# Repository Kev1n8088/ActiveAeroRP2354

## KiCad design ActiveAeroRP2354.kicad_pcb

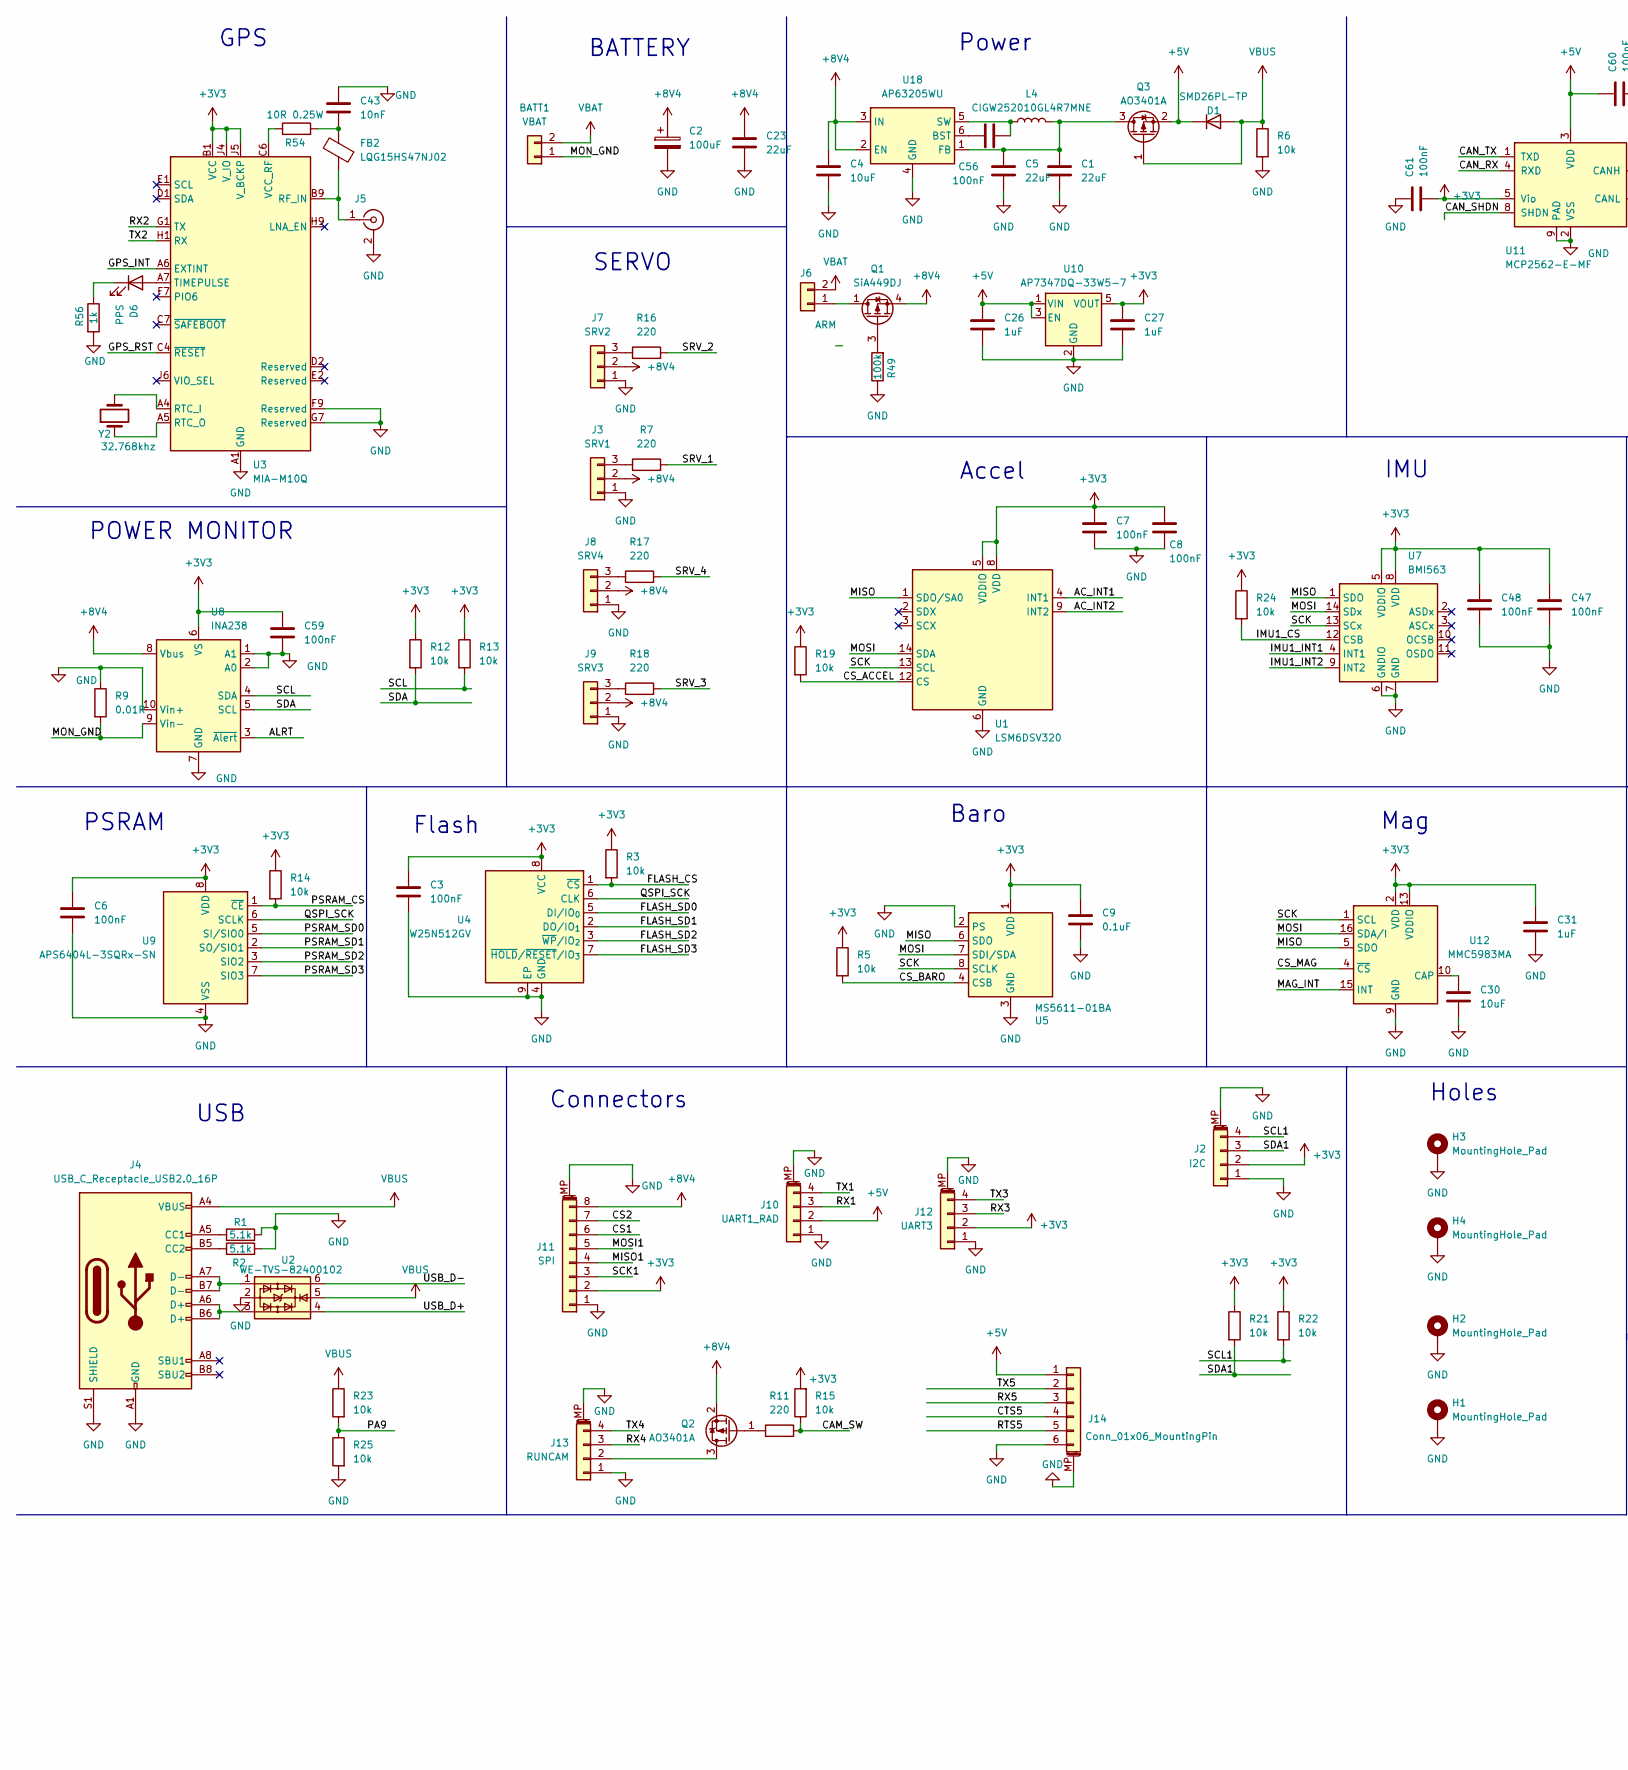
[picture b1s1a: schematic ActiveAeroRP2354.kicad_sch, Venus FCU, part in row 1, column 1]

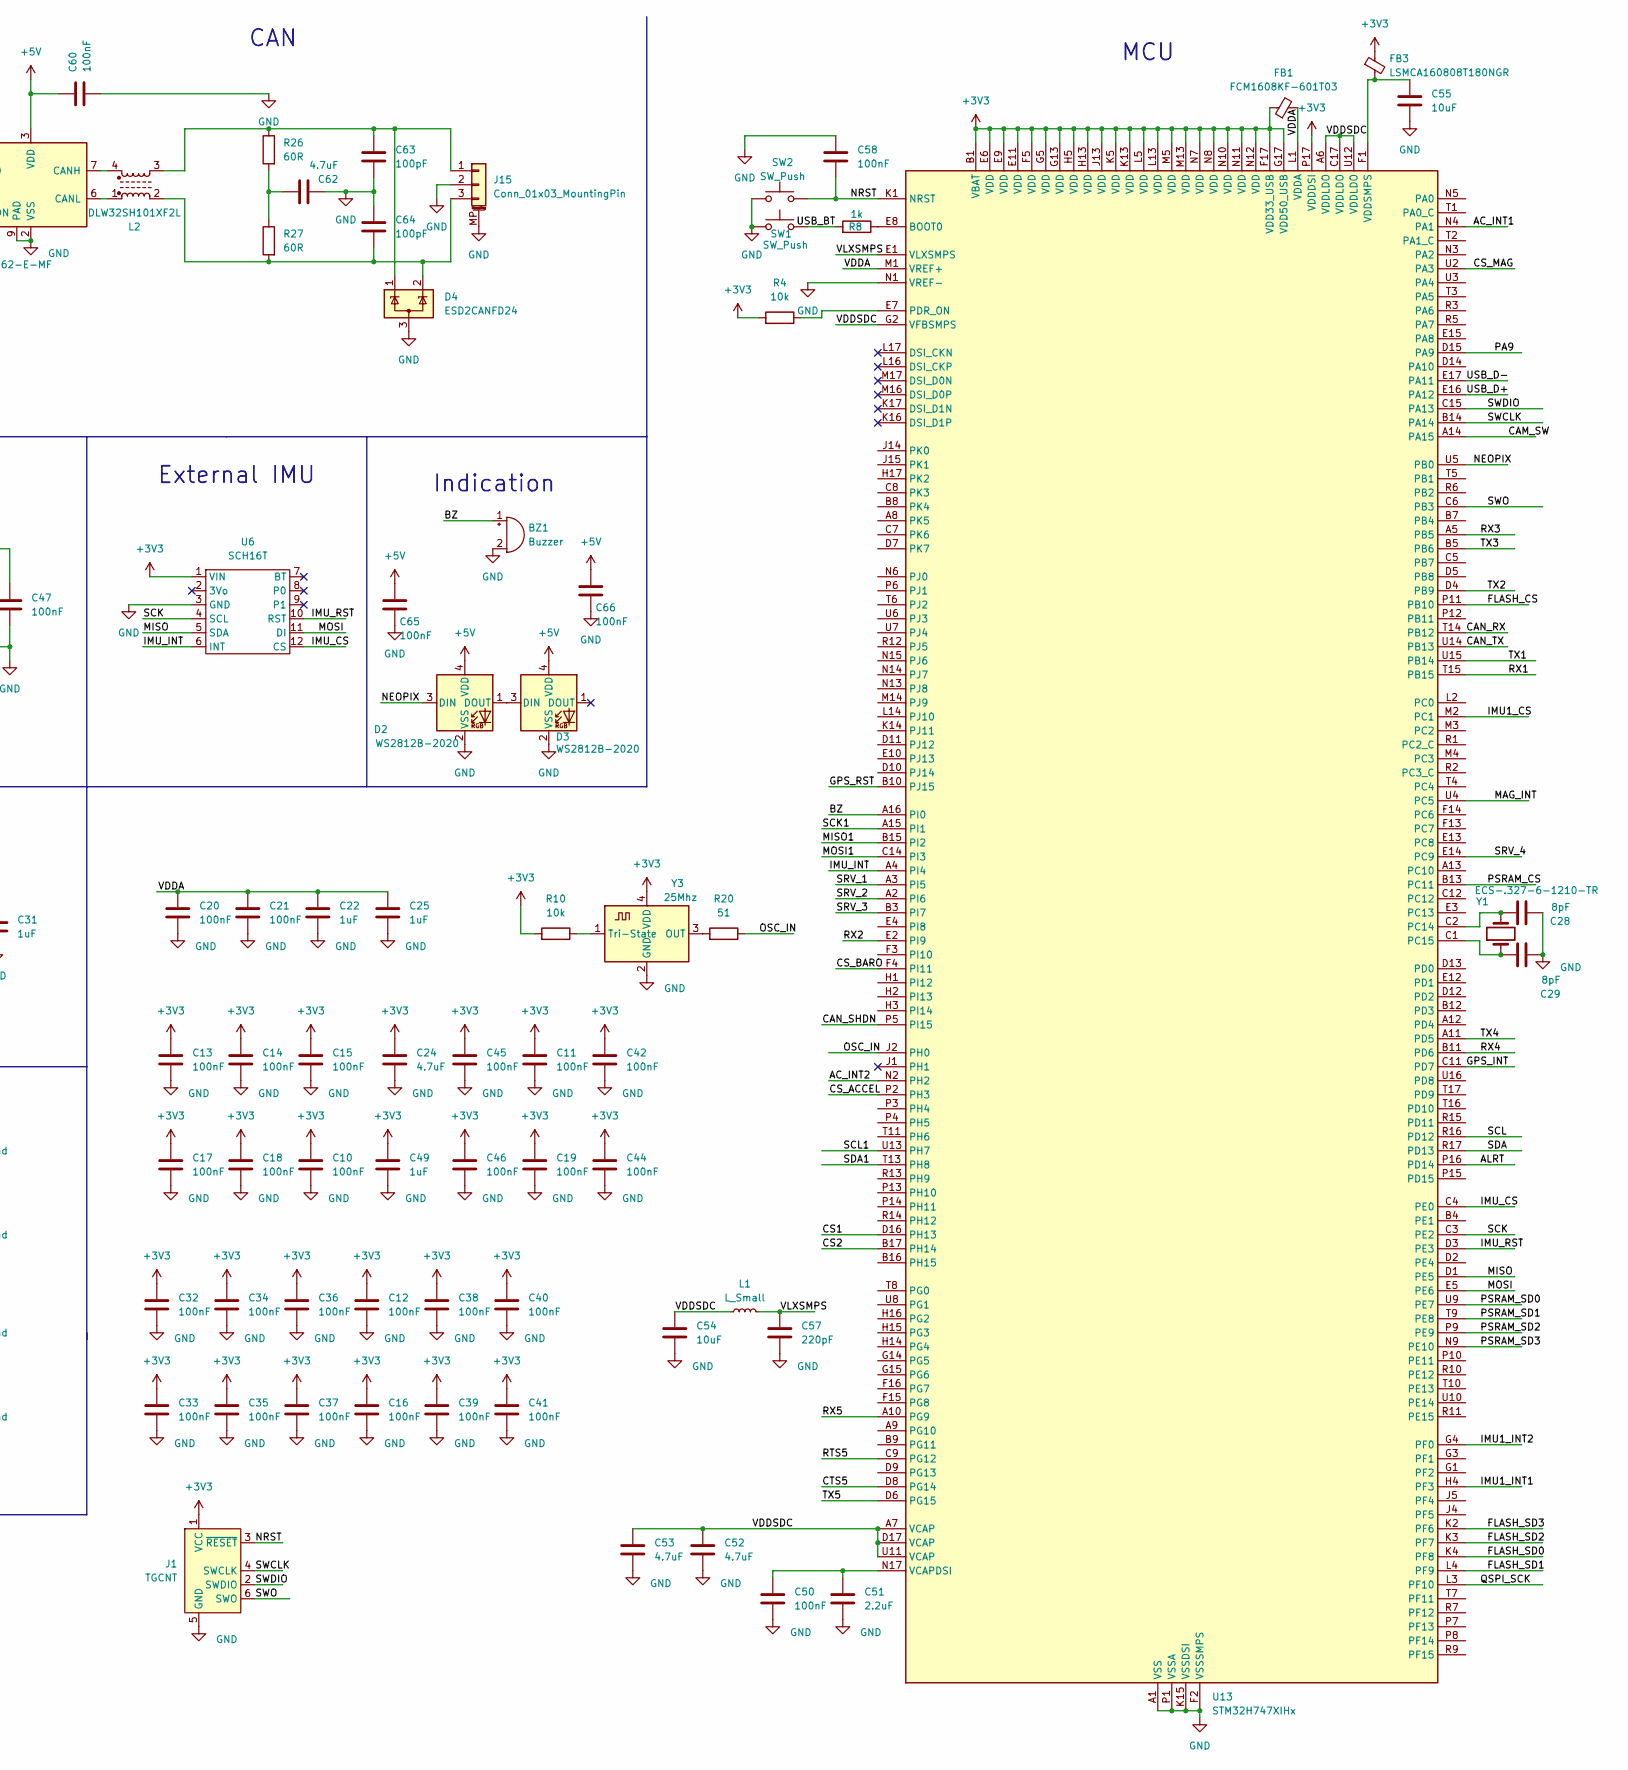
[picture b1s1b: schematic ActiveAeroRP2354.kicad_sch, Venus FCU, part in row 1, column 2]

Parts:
BATT1: VBAT; AMASS_XT30U-F_1x02_P5.0mm_Vertical
BZ1: Buzzer; Buzzer_CUI_CPT-9019S-SMT
C1, C5, C23: 22uF; C_0603_1608Metric
C2: 100uF; CP_Radial_D8.0mm_P5.00mm
C3, C6, C7, C8, C10, C11, C12, C13, C14, C15, C16, C17, C18, C19, C20, C21, C32, C33, C34, C35, C36, C37, C38, C39, C40, C41, C42, C44, C45, C46, C47, C48, C50, C56, C58, C59, C60, C61, C65, C66: 100nF; C_0402_1005Metric
C4, C30, C54, C55: 10uF; C_0402_1005Metric
C9: 0.1uF; C_0402_1005Metric
C22, C25, C26, C27, C31, C49: 1uF; C_0402_1005Metric
C24, C52, C53, C62: 4.7uF; C_0402_1005Metric
C28, C29: 8pF; C_0402_1005Metric
C43: 10nF; C_0402_1005Metric
C51: 2.2uF; C_0402_1005Metric
C57: 220pF; C_0402_1005Metric
C63, C64: 100pF; C_0402_1005Metric
D1: SMD26PL-TP; D_SOD-123F
D2, D3: WS2812B-2020; LED_WS2812B-2020_PLCC4_2.0x2.0mm
D4: ESD2CANFD24; SOT-23-3
D6: PPS; LED_0402_1005Metric
FB1: FCM1608KF-601T03; L_0402_1005Metric
FB2: LQG15HS47NJ02; L_0402_1005Metric
FB3: LSMCA160808T180NGR; L_0603_1608Metric
H1, H2, H3, H4: MountingHole_Pad; MountingHole_3.2mm_M3_DIN965_Pad
J1: TGCNT; Tag-Connect_TC2030-IDC-NL_2x03_P1.27mm_Vertical
J2: I2C; JST_SH_SM04B-SRSS-TB_1x04-1MP_P1.00mm_Horizontal
J3: SRV1; PinSocket_1x03_P2.54mm_Vertical
J4: USB_C_Receptacle_USB2.0_16P; USB_C_Receptacle_GCT_USB4110
J5: UFL; U.FL_Molex_MCRF_73412-0110_Vertical
J6: ARM; JST_PH_B2B-PH-K_1x02_P2.00mm_Vertical
J7: SRV2; PinSocket_1x03_P2.54mm_Vertical
J8: SRV4; PinSocket_1x03_P2.54mm_Vertical
J9: SRV3; PinSocket_1x03_P2.54mm_Vertical
J10: UART1_RAD; JST_GH_SM04B-GHS-TB_1x04-1MP_P1.25mm_Horizontal
J11: SPI; JST_GH_SM08B-GHS-TB_1x08-1MP_P1.25mm_Horizontal
J12: UART3; JST_GH_SM04B-GHS-TB_1x04-1MP_P1.25mm_Horizontal
J13: RUNCAM; JST_GH_SM04B-GHS-TB_1x04-1MP_P1.25mm_Horizontal
J14: Conn_01x06_MountingPin; JST_GH_SM06B-GHS-TB_1x06-1MP_P1.25mm_Horizontal
J15: Conn_01x03_MountingPin; JST_GH_SM03B-GHS-TB_1x03-1MP_P1.25mm_Horizontal
L1: L_Small; L_Changjiang_FTC201607S
L2: DLW32SH101XF2L; FIL_DLW32SH101XF2L
L4: CIGW252010GL4R7MNE; L_1008_2520Metric
Q1: SiA449DJ; Vishay_PowerPAK_SC70-6L_Single
Q2, Q3: AO3401A; SOT-23
R1, R2: 5.1k; R_0402_1005Metric
R3, R4, R5, R6, R10, R12, R13, R14, R15, R19, R21, R22, R23, R24, R25: 10k; R_0402_1005Metric
R7, R11, R16, R17, R18: 220; R_0402_1005Metric
R8, R56: 1k; R_0402_1005Metric
R9: 0.01R; R_2512_6332Metric
R20: 51; R_0402_1005Metric
R26, R27: 60R; R_0402_1005Metric
R49: 100k; R_0402_1005Metric
R54: 10R 0.25W; R_0402_1005Metric
SW1, SW2: SW_Push; SW_Push_SPST_NO_Alps_SKRK; LCSC C18077675
U1: LSM6DSV320; LGA-14_3x2.5mm_P0.5mm_LayoutBorder3x4y
U2: WE-TVS-82400102; SOT-23-6
U3: MIA-M10Q; ublox_LGA-53_4.5x4.5mm_Layout9x9_P0.5mm
U4: W25N512GV; WSON-8-1EP_6x5mm_P1.27mm_EP3.4x4.3mm
U5: MS5611-01BA; LGA-8_3x5mm_P1.25mm
U6: SCH16T; BNO085_Breakout_Footprint
U7: BMI563; Bosch_LGA-14_3x2.5mm_P0.5mm
U8: INA238; VSSOP-10_3x3mm_P0.5mm
U9: APS6404L-3SQRx-SN; SOIC-8_3.9x4.9mm_P1.27mm
U10: AP7347DQ-33W5-7; SOT-23-5
U11: MCP2562-E-MF; DFN-8-1EP_3x3mm_P0.65mm_EP1.55x2.4mm
U12: MMC5983MA; LGA-16_3x3mm_P0.5mm
U13: STM32H747XIHx; TFBGA-265_14x14mm_Layout17x17_P0.8mm
U18: AP63205WU; TSOT-23-6
Y1: ECS-.327-6-1210-TR; Crystal_SMD_MicroCrystal_CM9V-T1A-2Pin_1.6x1.0mm
Y2: 32.768khz; Crystal_SMD_MicroCrystal_CM9V-T1A-2Pin_1.6x1.0mm
Y3: 25Mhz; Oscillator_SMD_Abracon_ASCO-4Pin_1.6x1.2mm

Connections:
+3V3: C3.1, C6.1, C7.2, C8.2, C9.2, C10.1, C11.1, C12.1, C13.1, C14.1, C15.1, C16.1, C17.1, C18.1, C19.1, C24.1, C27.1, C31.2, C32.1, C33.1, C34.1, C35.1, C36.1, C37.1, C38.1, C39.1, C40.1, C41.1, C42.1, C44.1, C45.1, C46.1, C47.1, C48.1, C49.1, C59.1, C61.2, FB1.1, FB3.1, J1.1 (VCC), J2.2, J11.2, J12.2, R3.1, R4.2, R5.1, R10.2, R12.1, R13.1, R14.1, R15.2, R19.1, R21.1, R22.1, R24.1, U1.5 (VDDIO), U1.8 (VDD), U3.B1 (VCC), U3.J4 (V_IO), U3.J5 (V_BCKP), U4.8 (VCC), U5.1 (VDD), U6.1 (VIN), U7.5 (VDDIO), U7.8 (VDD), U8.6 (VS), U9.8 (VDD), U10.5 (VOUT), U11.5 (Vio), U12.2 (VDD), U12.13 (VDDIO), U13.B1 (VBAT), U13.E6 (VDD), U13.E9 (VDD), U13.E11 (VDD), U13.F5 (VDD), U13.F17 (VDD33_USB), U13.G5 (VDD), U13.G13 (VDD), U13.G17 (VDD50_USB), U13.H5 (VDD), U13.H13 (VDD), U13.J13 (VDD), U13.K5 (VDD), U13.K13 (VDD), U13.L5 (VDD), U13.L13 (VDD), U13.M5 (VDD), U13.M13 (VDD), U13.N7 (VDD), U13.N8 (VDD), U13.N10 (VDD), U13.N11 (VDD), U13.N12 (VDD), U13.P17 (VDDDSI), Y3.4 (VDD)
+5V: C26.1, C60.1, C65.2, C66.2, D1.1 (K), D2.4 (VDD), D3.4 (VDD), J10.2, J14.1, Q3.2 (S), U10.1 (VIN), U10.3 (EN), U11.3 (VDD)
+8V4: C2.1, C4.1, C23.1, J3.2, J7.2, J8.2, J9.2, J11.8, Q1.4 (S), Q2.2 (S), U8.8 (Vbus), U18.2 (EN), U18.3 (IN)
/AC_INT1: U1.4 (INT1), U13.N4 (PA1)
/AC_INT2: U1.9 (INT2), U13.N2 (PH2)
/ALRT: U8.3 (~Alert), U13.P16 (PD14)
/BZ: BZ1.1 (+), U13.A16 (PI0)
/CAM_SW: R11.2, R15.1, U13.A14 (PA15)
/CAN_RX: U11.4 (RXD), U13.T14 (PB12)
/CAN_SHDN: U11.8 (SHDN), U13.P5 (PI15)
/CAN_TX: U11.1 (TXD), U13.U14 (PB13)
/CS1: J11.6, U13.D16 (PH13)
/CS2: J11.7, U13.B17 (PH14)
/CS_ACCEL: R19.2, U1.12 (CS), U13.P2 (PH3)
/CS_BARO: R5.2, U5.4 (CSB), U5.5 (CSB), U13.F4 (PI11)
/CS_MAG: U12.4 (~CS), U13.U2 (PA3)
/CTS5: J14.4, U13.D8 (PG14)
/FLASH_CS: R3.2, U4.1 (~CS), U13.P11 (PB10)
/FLASH_SD0: U4.5 (DI/IO_{0}), U13.K4 (PF8)
/FLASH_SD1: U4.2 (DO/IO_{1}), U13.L4 (PF9)
/FLASH_SD2: U4.3 (~WP/IO_{2}), U13.K3 (PF7)
/FLASH_SD3: U4.7 (~HOLD/~RESET/IO_{3}), U13.K2 (PF6)
/GPS_INT: U3.A6 (EXTINT), U13.C11 (PD7)
/GPS_RST: U3.C4 (~RESET), U13.B10 (PJ15)
/IMU1_CS: R24.2, U7.12 (CSB), U13.M2 (PC1)
/IMU1_INT1: U7.4 (INT1), U13.H4 (PF3)
/IMU1_INT2: U7.9 (INT2), U13.G4 (PF0)
/IMU_CS: U6.12 (CS), U13.C4 (PE0)
/IMU_INT: U6.6 (INT), U13.A4 (PI4)
/IMU_RST: U6.10 (RST), U13.D3 (PE3)
/MAG_INT: U12.15 (INT), U13.U4 (PC5)
/MISO: U1.1 (SDO/SA0), U5.6 (SDO), U6.5 (SDA), U7.1 (SDO), U12.5 (SDO), U13.D1 (PE5)
/MISO1: J11.4, U13.B15 (PI2)
/MON_GND: BATT1.1, R9.2, U8.9 (Vin-)
/MOSI: U1.14 (SDA), U5.7 (SDI/SDA), U6.11 (DI), U7.14 (SDx), U12.16 (SDA/I), U13.E5 (PE6)
/MOSI1: J11.5, U13.C14 (PI3)
/NEOPIX: D2.3 (DIN), U13.U5 (PB0)
/NRST: C58.1, J1.3 (~RESET), SW2.1, U13.K1 (NRST)
/OSC_IN: R20.1, U13.J2 (PH0)
/PA9: R23.2, R25.1, U13.D15 (PA9)
/PSRAM_CS: R14.2, U9.1 (~CE), U13.B13 (PC11)
/PSRAM_SD0: U9.5 (SI/SIO0), U13.U9 (PE7)
/PSRAM_SD1: U9.2 (SO/SIO1), U13.T9 (PE8)
/PSRAM_SD2: U9.3 (SIO2), U13.P9 (PE9)
/PSRAM_SD3: U9.7 (SIO3), U13.N9 (PE10)
/QSPI_SCK: U4.6 (CLK), U9.6 (SCLK), U13.L3 (PF10)
/RTS5: J14.5, U13.C9 (PG12)
/RX1: J10.3, U13.T15 (PB15)
/RX2: U3.G1 (TX), U13.E2 (PI9)
/RX3: J12.3, U13.A5 (PB5)
/RX4: J13.3, U13.B11 (PD6)
/RX5: J14.3, U13.A10 (PG9)
/SCK: U1.13 (SCL), U5.8 (SCLK), U6.4 (SCL), U7.13 (SCx), U12.1 (SCL), U13.C3 (PE2)
/SCK1: J11.3, U13.A15 (PI1)
/SCL: R13.2, U8.4 (SDA), U13.R16 (PD12)
/SCL1: J2.4, R22.2, U13.U13 (PH7)
/SDA: R12.2, U8.5 (SCL), U13.R17 (PD13)
/SDA1: J2.3, R21.2, U13.T13 (PH8)
/SRV_1: R7.2, U13.A3 (PI5)
/SRV_2: R16.2, U13.A2 (PI6)
/SRV_3: R18.2, U13.B3 (PI7)
/SRV_4: R17.2, U13.E14 (PC9)
/SWCLK: J1.4 (SWCLK), U13.B14 (PA14)
/SWDIO: J1.2 (SWDIO), U13.C15 (PA13)
/SWO: J1.6 (SWO), U13.C6 (PB3)
/TX1: J10.4, U13.U15 (PB14)
/TX2: U3.H1 (RX), U13.D4 (PB9)
/TX3: J12.4, U13.B5 (PB6)
/TX4: J13.4, U13.A11 (PD5)
/TX5: J14.2, U13.D6 (PG15)
/USB_BT: R8.2, SW1.1
/USB_D+: U2.4, U13.E16 (PA12)
/USB_D-: U2.6, U13.E17 (PA11)
/VDDA: C20.1, C21.1, C22.1, C25.1, FB1.2, U13.L1 (VDDA), U13.M1 (VREF+)
/VDDSDC: C52.1, C53.1, C54.1, L1.1, U13.A6 (VDDLDO), U13.A7 (VCAP), U13.C17 (VDDLDO), U13.D17 (VCAP), U13.G2 (VFBSMPS), U13.U11 (VCAP), U13.U12 (VDDLDO)
/VLXSMPS: C57.1, L1.2, U13.E1 (VLXSMPS)
GND: BZ1.2 (-), C1.2, C2.2, C3.2, C4.2, C5.2, C6.2, C7.1, C8.1, C9.1, C10.2, C11.2, C12.2, C13.2, C14.2, C15.2, C16.2, C17.2, C18.2, C19.2, C20.2, C21.2, C22.2, C23.2, C24.2, C25.2, C26.2, C27.2, C28.2, C29.2, C30.1, C31.1, C32.2, C33.2, C34.2, C35.2, C36.2, C37.2, C38.2, C39.2, C40.2, C41.2, C42.2, C43.2, C44.2, C45.2, C46.2, C47.2, C48.2, C49.2, C50.2, C51.2, C52.2, C53.2, C54.2, C55.1, C57.2, C58.2, C59.2, C60.2, C61.1, C62.2, C63.2, C64.1, C65.1, C66.1, D2.2 (VSS), D3.2 (VSS), D4.3 (A), H1.1, H2.1, H3.1, H4.1, J1.5 (GND), J2.1, J2.MP (MountPin), J3.1, J4.A1 (GND), J4.A12 (GND), J4.B1 (GND), J4.B12 (GND), J4.S1 (SHIELD), J5.2 (Ext), J7.1, J8.1, J9.1, J10.1, J10.MP (MountPin), J11.1, J11.MP (MountPin), J12.1, J12.MP (MountPin), J13.1, J13.MP (MountPin), J14.6, J14.MP (MountPin), J15.2, J15.MP (MountPin), R1.2, R2.2, R6.2, R9.1, R25.2, R49.1, R56.2, SW1.2, SW2.2, U1.6 (GND), U1.7 (GND), U2.2, U3.A1 (GND), U3.A2 (GND), U3.A3 (GND), U3.A8 (GND), U3.A9 (GND), U3.B2 (GND), U3.B8 (GND), U3.C3 (GND), U3.C9 (GND), U3.E3 (GND), U3.E4 (GND), U3.E9 (GND), U3.F1 (GND), U3.F3 (GND), U3.F4 (GND), U3.F9 (Reserved), U3.G3 (GND), U3.G4 (GND), U3.G5 (GND), U3.G6 (GND), U3.G7 (Reserved), U3.H8 (GND), U3.J8 (GND), U3.J9 (GND), U4.4 (GND), U4.9 (EP), U5.2 (PS), U5.3 (GND), U6.3 (GND), U7.6 (GNDIO), U7.7 (GND), U8.1 (A1), U8.2 (A0), U8.7 (GND), U8.10 (Vin+), U9.4 (VSS), U10.2 (GND), U11.2 (VSS), U11.9 (PAD), U12.9 (GND), U12.11 (GND), U13.A1 (VSS), U13.A17 (VSS), U13.B2 (VSS), U13.B6 (VSS), U13.C10 (VSS), U13.C13 (VSS), U13.C16 (VSS), U13.F2 (VSSSMPS), U13.G7 (VSS), U13.G8 (VSS), U13.G9 (VSS), U13.G10 (VSS), U13.G11 (VSS), U13.G16 (VSS), U13.H7 (VSS), U13.H8 (VSS), U13.H9 (VSS), U13.H10 (VSS), U13.H11 (VSS), U13.J3 (VSS), U13.J7 (VSS), U13.J8 (VSS), U13.J9 (VSS), U13.J10 (VSS), U13.J11 (VSS), U13.J16 (VSS), U13.J17 (VSS), U13.K7 (VSS), U13.K8 (VSS), U13.K9 (VSS), U13.K10 (VSS), U13.K11 (VSS), U13.K15 (VSSDSI), U13.L7 (VSS), U13.L8 (VSS), U13.L9 (VSS), U13.L10 (VSS), U13.L11 (VSS), U13.L15 (VSSDSI), U13.M15 (VSSDSI), U13.N1 (VREF-), U13.N16 (VSS), U13.P1 (VSSA), U13.R4 (VSS), U13.R8 (VSS), U13.T12 (VSS), U13.U1 (VSS), U13.U17 (VSS), U18.4 (GND), Y3.2 (GND)
unnamed: C43.1, FB2.2, R54.2
unnamed: C62.1, R26.2, R27.1
unnamed: D2.1 (DOUT), D3.3 (DIN)
unnamed: D6.2 (A), U3.A7 (TIMEPULSE)
unnamed: D6.1 (K), R56.1
unnamed: J3.3, R7.1
unnamed: J4.A5 (CC1), R1.1
unnamed: J4.B5 (CC2), R2.1
unnamed: J4.A6 (D+), J4.B6 (D+), U2.3
unnamed: J4.A7 (D-), J4.B7 (D-), U2.1
unnamed: FB2.1, J5.1 (In), U3.B9 (RF_IN)
unnamed: J6.1, Q1.1 (D)
unnamed: J7.3, R16.1
unnamed: J8.3, R17.1
unnamed: J9.3, R18.1
unnamed: J13.2, Q2.3 (D)
unnamed: C63.1, D4.1 (K), J15.1, L2.3, R26.1
unnamed: C64.2, D4.2 (K), J15.3, L2.2, R27.2
unnamed: Q1.3 (G), R49.2
unnamed: Q2.1 (G), R11.1
unnamed: C1.1, C5.1, L4.2, Q3.3 (D), U18.1 (FB)
unnamed: U3.A4 (RTC_I), Y2.2
unnamed: U3.A5 (RTC_O), Y2.1
unnamed: R54.1, U3.C6 (VCC_RF)
unnamed: L2.4, U11.7 (CANH)
unnamed: L2.1, U11.6 (CANL)
unnamed: C30.2, U12.10 (CAP)
unnamed: R8.1, U13.E8 (BOOT0)
unnamed: C28.1, U13.C2 (PC14), Y1.2
unnamed: C29.1, U13.C1 (PC15), Y1.1
unnamed: R4.1, U13.E7 (PDR_ON)
unnamed: C50.1, C51.1, U13.N17 (VCAPDSI)
unnamed: C55.2, FB3.2, U13.F1 (VDDSMPS)
unnamed: C56.1, U18.6 (BST)
unnamed: C56.2, L4.1, U18.5 (SW)
unnamed: R20.2, Y3.3 (OUT)
unnamed: R10.1, Y3.1 (Tri-State)
VBAT: BATT1.2, J6.2
VBUS: D1.2 (A), J4.A4 (VBUS), J4.A9 (VBUS), J4.B4 (VBUS), J4.B9 (VBUS), Q3.1 (G), R6.1, R23.1, U2.5

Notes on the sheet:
USB
CAN
IMU
Holes
GPS
SERVO
BATTERY
Accel
Mag
POWER MONITOR
Baro
MCU
Connectors
External IMU
Power
Flash
PSRAM
Indication

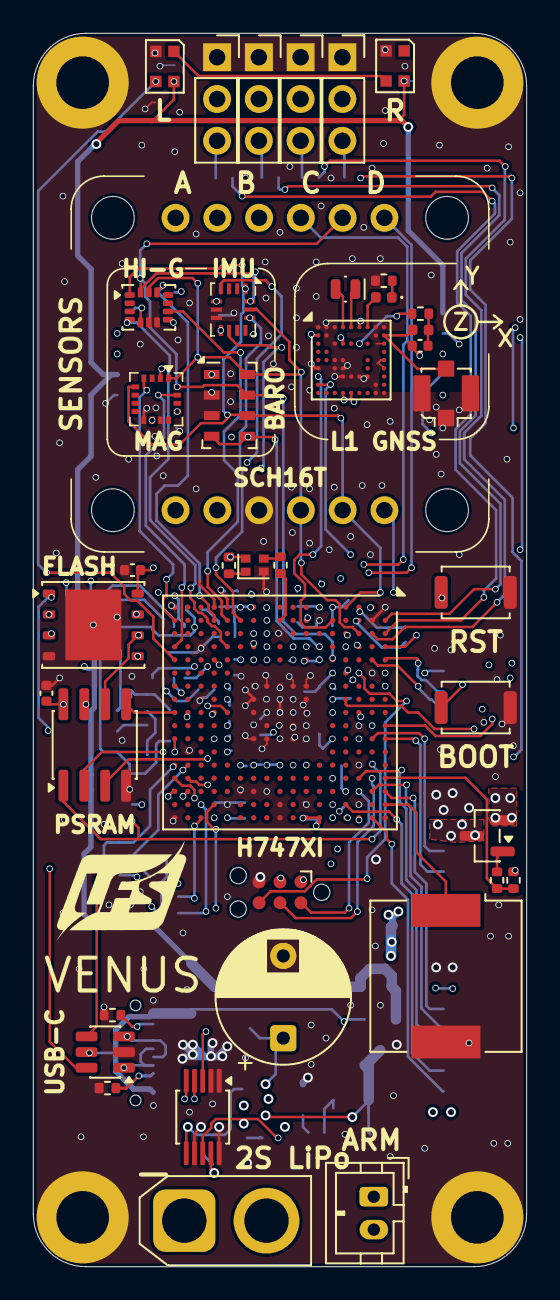
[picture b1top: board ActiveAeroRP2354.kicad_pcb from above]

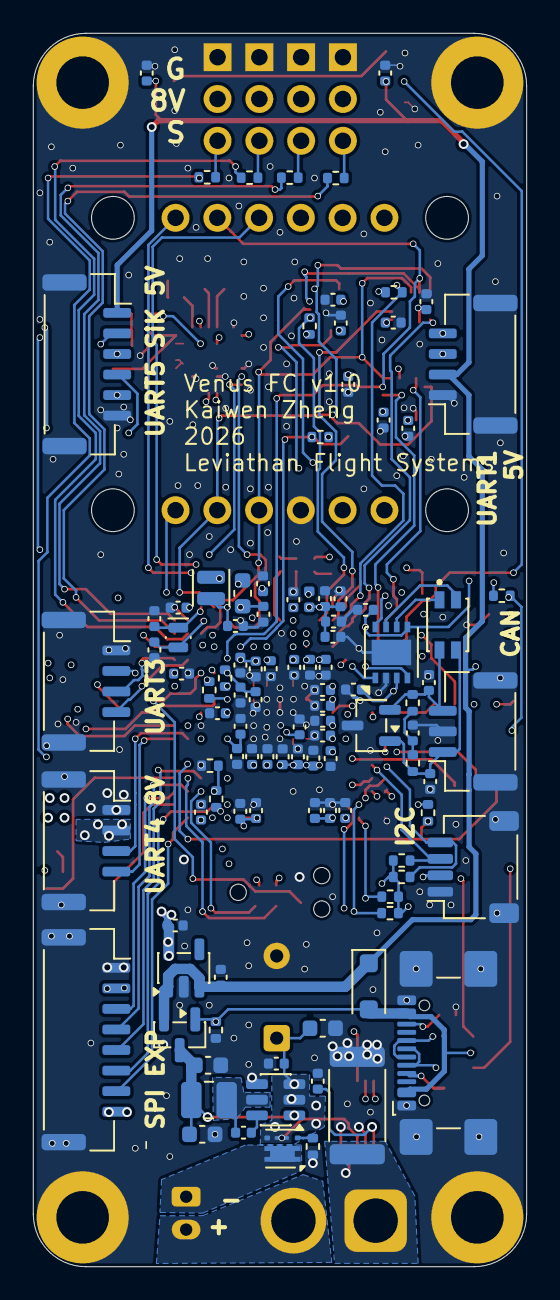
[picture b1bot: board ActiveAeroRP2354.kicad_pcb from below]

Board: 6 copper layers, 30.0 x 75.0 mm, 150 parts (105 on the bottom side), 116 nets.

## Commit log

2026-02-18 mcu schematic done
2026-02-18 added gitignore
2026-02-18 basic routing done
2026-02-19 switched to double sided stm32h747xi
2026-02-19 design lock (probably), added silks
2026-02-20 cleaned up silkscreens and layout
2026-02-20 finished silks
